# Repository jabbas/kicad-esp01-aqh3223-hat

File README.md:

# esp01-aqh3223-hat

# Schema

# PCB

# Render front

# Render back

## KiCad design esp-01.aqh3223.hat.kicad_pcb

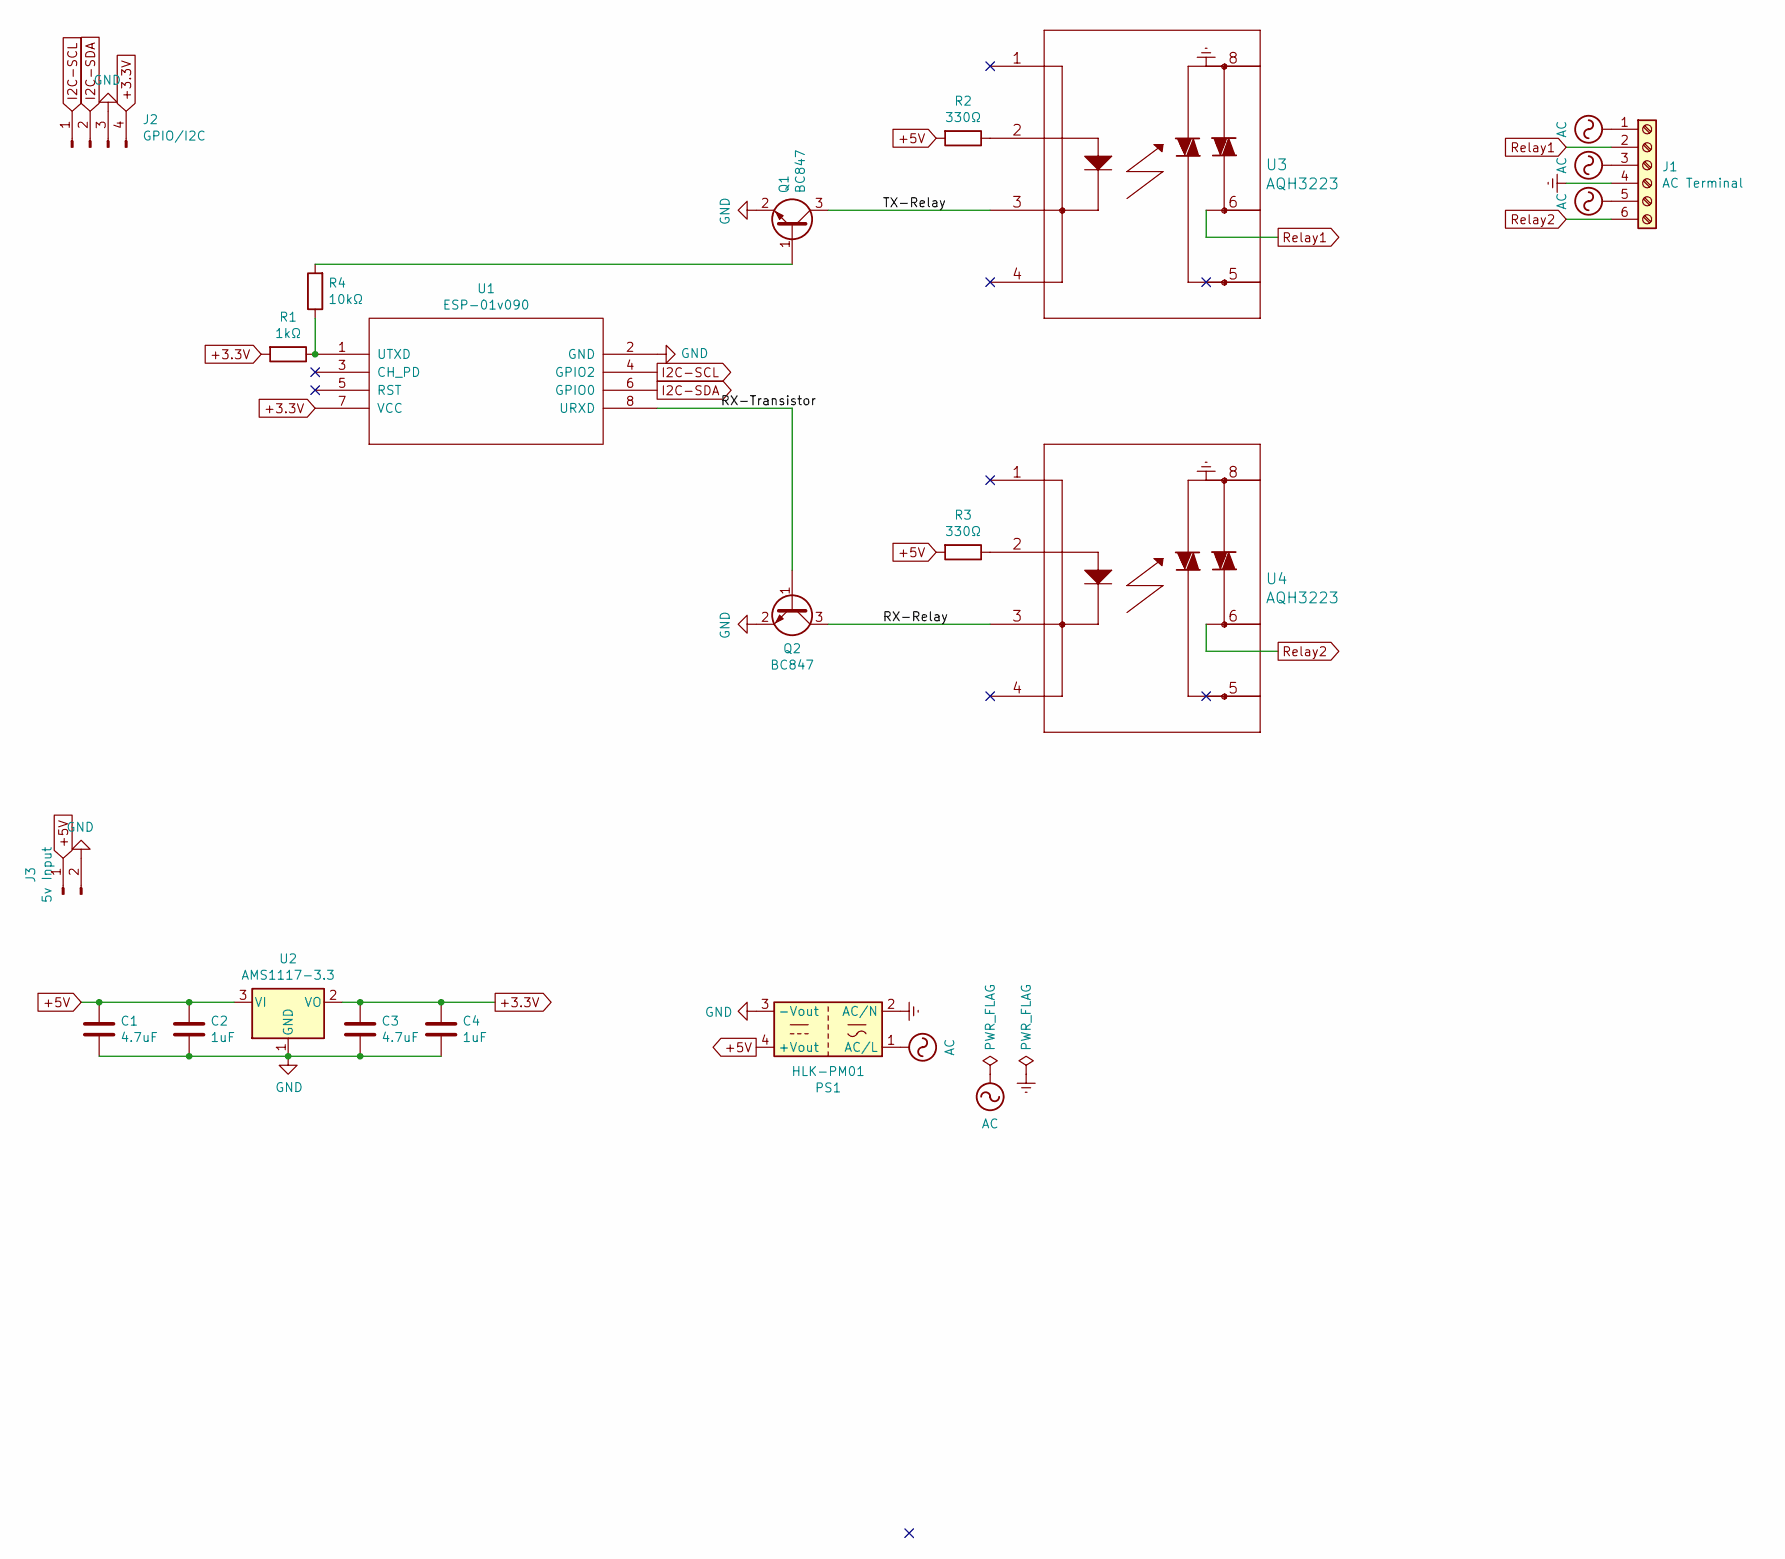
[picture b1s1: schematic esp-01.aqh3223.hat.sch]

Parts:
C1, C3: 4.7uF; C_0805_2012Metric_Pad1.15x1.40mm_HandSolder
C2, C4: 1uF; C_0805_2012Metric_Pad1.15x1.40mm_HandSolder
J1: AC Terminal; TerminalBlock_bornier-6_P5.08mm
J2: GPIO/I2C; PinHeader_1x04_P2.54mm_Vertical
J3: 5v Input; PinSocket_1x02_P2.54mm_Vertical
PS1: HLK-PM01; Converter_ACDC_HiLink_HLK-PMxx
Q1, Q2: BC847; SOT-23
R1: 1kΩ; R_0805_2012Metric_Pad1.15x1.40mm_HandSolder
R2, R3: 330Ω; R_0805_2012Metric_Pad1.15x1.40mm_HandSolder
R4: 10kΩ; R_0805_2012Metric_Pad1.15x1.40mm_HandSolder
U1: ESP-01v090; ESP-01
U2: AMS1117-3.3; SOT-223-3_TabPin2
U3, U4: AQH3223

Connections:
+3.3V: C3.1, C4.1, J2.4, R1.2, U1.7 (VCC), U2.2 (VO)
+5V: C1.1, C2.1, J3.1, PS1.4 (+Vout), R2.2, R3.2, U2.3 (VI)
/RX-Relay: Q2.3 (C), U4.3
/RX-Transistor: Q2.1 (B), U1.8 (URXD)
/TX-Relay: Q1.3 (C), U3.3
AC: J1.1, J1.3, J1.5, PS1.1 (AC/L)
Earth: J1.4, PS1.2 (AC/N), U3.8, U4.8
GND: C1.2, C2.2, C3.2, C4.2, J2.3, J3.2, PS1.3 (-Vout), Q1.2 (E), Q2.2 (E), U1.2 (GND), U2.1 (GND)
I2C-SCL: J2.1, U1.4 (GPIO2)
I2C-SDA: J2.2, U1.6 (GPIO0)
unnamed: Q1.1 (B), R4.2
unnamed: R1.1, R4.1, U1.1 (UTXD)
unnamed: R2.1, U3.2
unnamed: R3.1, U4.2
Relay1: J1.2, U3.6
Relay2: J1.6, U4.6

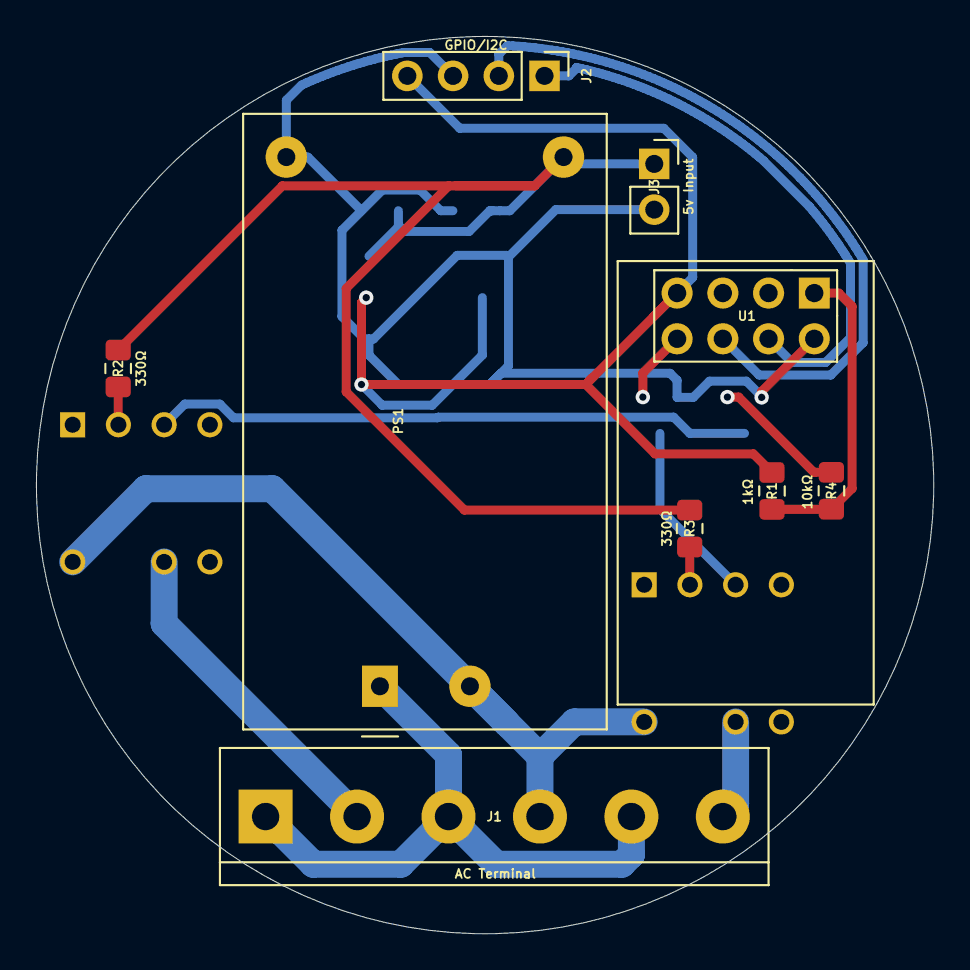
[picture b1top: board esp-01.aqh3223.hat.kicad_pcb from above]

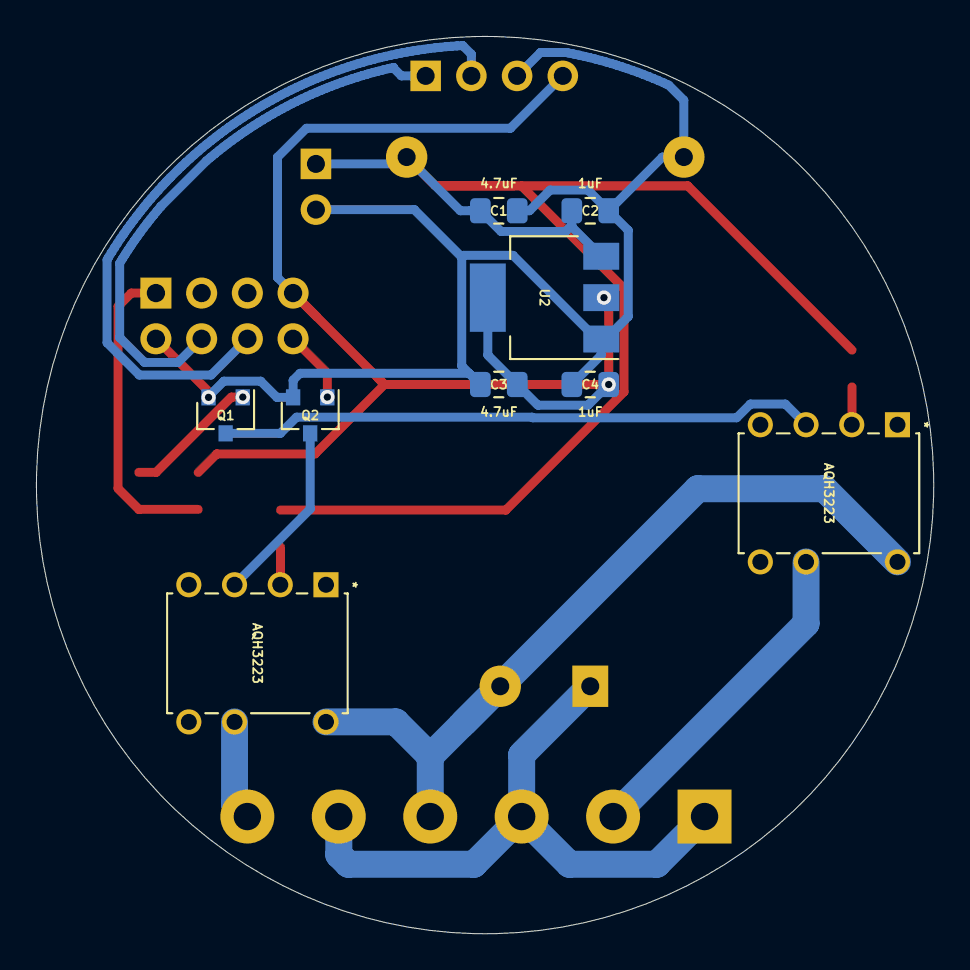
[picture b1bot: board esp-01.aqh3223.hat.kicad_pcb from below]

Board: 2 copper layers, 49.8 x 49.8 mm, 18 parts (9 on the bottom side), 16 nets.

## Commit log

2020-05-14 adds initial version of the board
2020-05-14 adds back render
2020-08-05 fixed booting of esp-01
2020-08-05 updated png files
